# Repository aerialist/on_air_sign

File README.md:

# on_air_sign
An ON_AIR sign board with RGB LED matrix and a separate controller 

# make secret.py file
You would need to make secret.py file with following contents:

secrets = {
    'ssid' : 'yourssid', # home wifi access point ssid
    'password' : 'ssidpassword', # password for ssid
    'timezone' : "Asia/Tokyo", # http://worldtimeapi.org/timezones
    'aio_username': "aiouser", # Adafruit IO user name
    'aio_password': "aiokey", # Adafruit IO password
    'broker': "awsiotxxx.amazonaws.com", # AWS IoT Device data endpoint
    "client_id": "on_air_sign_featherm4", # AWS IoT Things name for testing
    "client_id_controller": "on_air_sign_controller", # AWS IoT Things name for controller
    "client_id_matrix": "on_air_sign_matrix", # AWS IoT Things name for matrix
}

# copy AWS IoT device certificates and private keys

Define AWS IoT Thing for controller and matrix. Download device certificates and private keys in aws folder.

aws/aws_cert_controller.pem.crt
aws/aws_cert_matrix.pem.crt
aws/private_controller.pem.key
aws/private_matrix.pem.key

# code to use Adafruit IO

code_controller.py
code_matrix.py

Copy them as code.py to controller and matrix.

# code to use AWS IoT

code_controller_aws.py
code_matrix_aws.py

Copy them as code.py to controller and matrix.

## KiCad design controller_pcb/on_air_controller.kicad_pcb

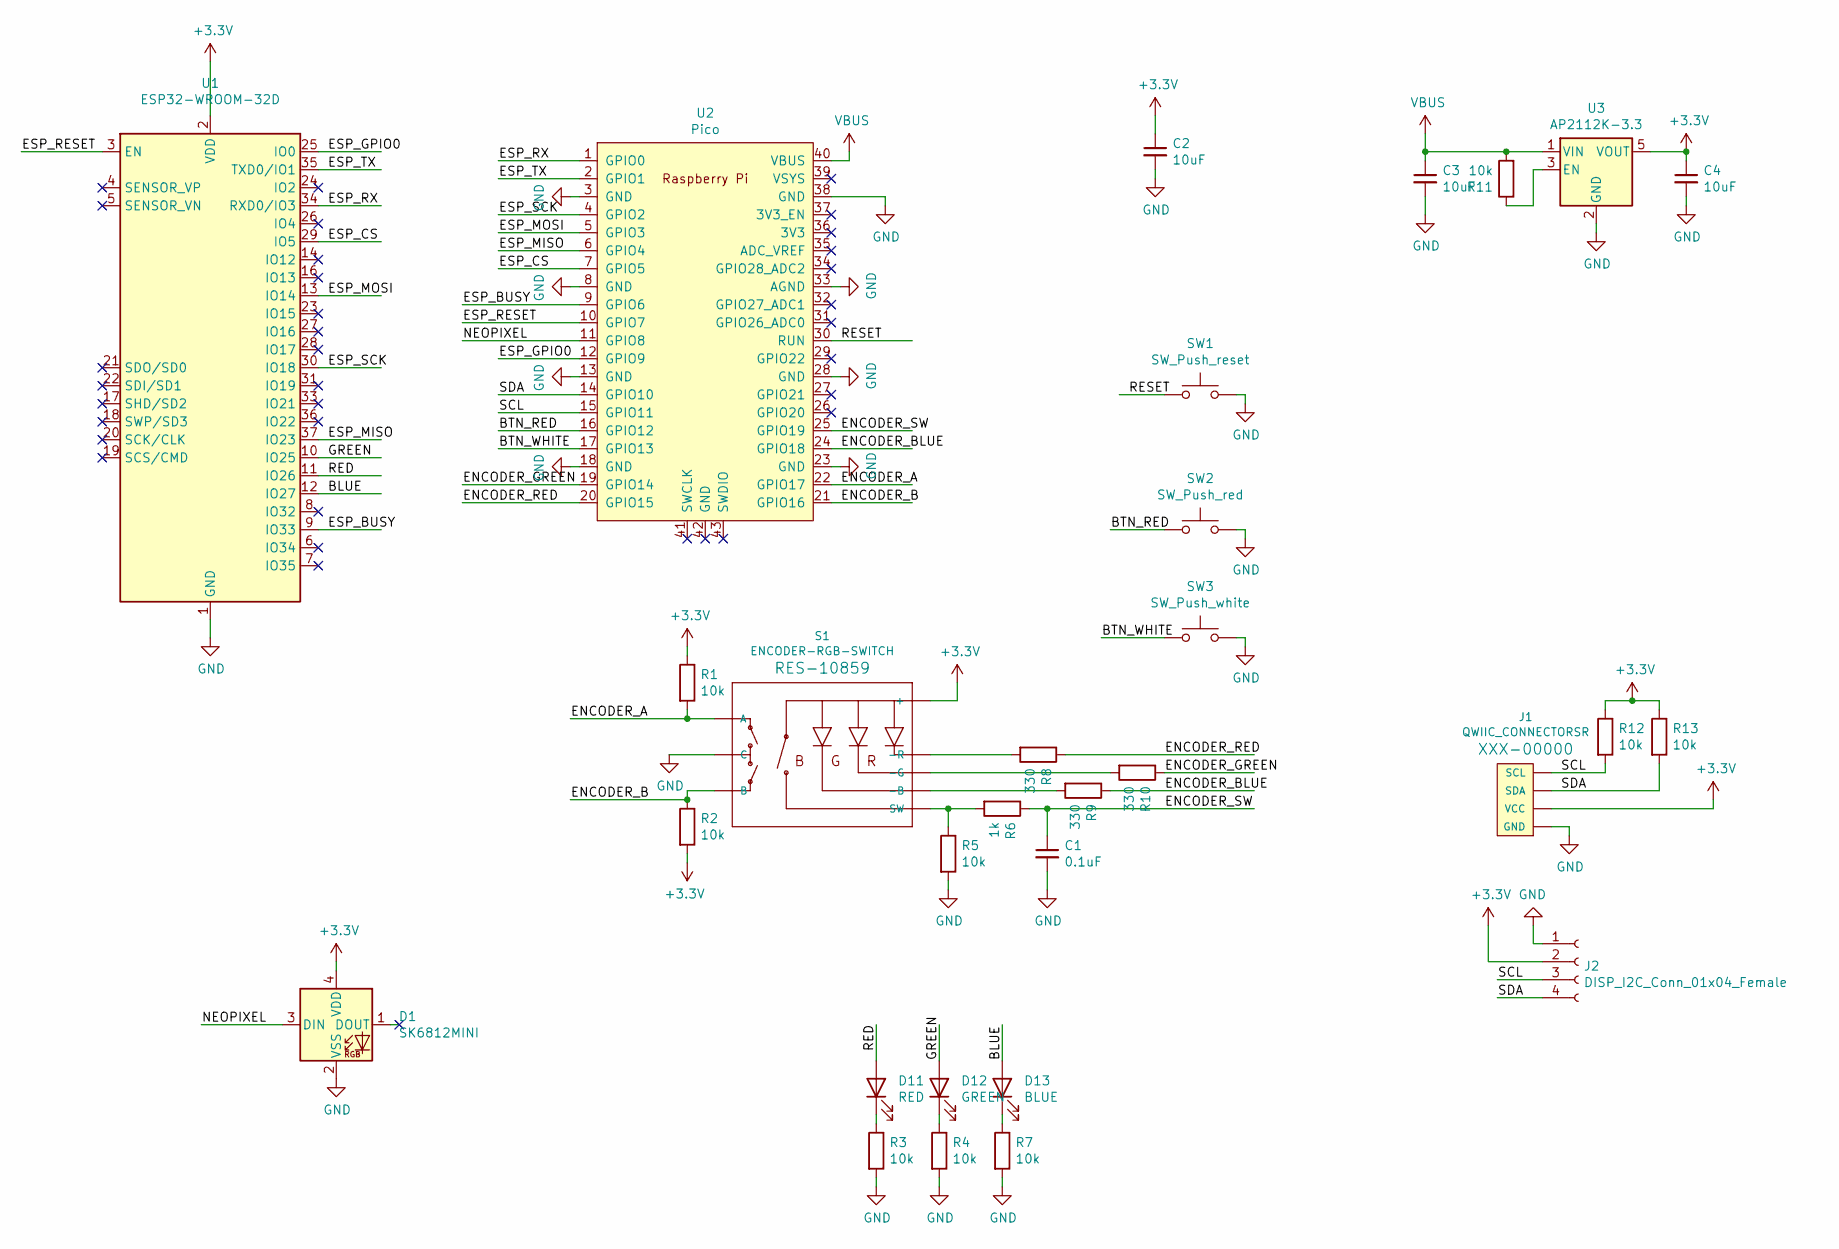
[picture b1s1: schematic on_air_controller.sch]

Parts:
C1: 0.1uF; C_0805_2012Metric_Pad1.18x1.45mm_HandSolder
C2, C3, C4: 10uF; C_0805_2012Metric_Pad1.18x1.45mm_HandSolder
D1: SK6812MINI; LED_SK6812MINI_PLCC4_3.5x3.5mm_P1.75mm
D11: RED; LED_1206_3216Metric_Pad1.42x1.75mm_HandSolder
D12: GREEN; LED_1206_3216Metric_Pad1.42x1.75mm_HandSolder
D13: BLUE; LED_1206_3216Metric_Pad1.42x1.75mm_HandSolder
J1: QWIIC_CONNECTORSR; 1X04_1MM_RA_STRESSRELIEF
J2: DISP_I2C_Conn_01x04_Female; OLED_0.96inch_PinHeader_1x04_P2.54mm_Vertical
R1, R2, R3, R4, R5, R7, R11, R12, R13: 10k; R_0805_2012Metric_Pad1.20x1.40mm_HandSolder
R6: 1k; R_0805_2012Metric_Pad1.20x1.40mm_HandSolder
R8, R9, R10: 330; R_0805_2012Metric_Pad1.20x1.40mm_HandSolder
S1: ENCODER-RGB-SWITCH; ENCODER_LED_3
SW1: SW_Push_reset; SW_Push_1P1T_NO_CK_KMR2
SW2: SW_Push_red; SW_Cherry_MX_1.00u_PCB
SW3: SW_Push_white; SW_Cherry_MX_1.00u_PCB
U1: ESP32-WROOM-32D; ESP32-WROOM-32
U2: Pico; RPi_Pico_SMD_TH
U3: AP2112K-3.3; SOT-23-5

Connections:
+3V3: C2.1, C4.1, D1.4 (VDD), J1.2 (VCC), J2.2, R1.1, R2.2, R12.1, R13.1, S1.5 (+), U1.2 (VDD), U3.5 (VOUT)
/BLUE: D13.2 (A), U1.12 (IO27)
/BTN_RED: SW2.1, U2.16 (GPIO12)
/BTN_WHITE: SW3.1, U2.17 (GPIO13)
/ENCODER_A: R1.2, S1.A, U2.22 (GPIO17)
/ENCODER_B: R2.1, S1.B, U2.21 (GPIO16)
/ENCODER_BLUE: R9.1, U2.24 (GPIO18)
/ENCODER_GREEN: R10.1, U2.19 (GPIO14)
/ENCODER_RED: R8.1, U2.20 (GPIO15)
/ENCODER_SW: C1.1, R6.1, U2.25 (GPIO19)
/ESP_BUSY: U1.9 (IO33), U2.9 (GPIO6)
/ESP_CS: U1.29 (IO5), U2.7 (GPIO5)
/ESP_GPIO0: U1.25 (IO0), U2.12 (GPIO9)
/ESP_MISO: U1.37 (IO23), U2.6 (GPIO4)
/ESP_MOSI: U1.13 (IO14), U2.5 (GPIO3)
/ESP_RESET: U1.3 (EN), U2.10 (GPIO7)
/ESP_RX: U1.34 (RXD0/IO3), U2.1 (GPIO0)
/ESP_SCK: U1.30 (IO18), U2.4 (GPIO2)
/ESP_TX: U1.35 (TXD0/IO1), U2.2 (GPIO1)
/GREEN: D12.2 (A), U1.10 (IO25)
/NEOPIXEL: D1.3 (DIN), U2.11 (GPIO8)
/RED: D11.2 (A), U1.11 (IO26)
/RESET: SW1.1, U2.30 (RUN)
/SCL: J1.4 (SCL), J2.3, R12.2, U2.15 (GPIO11)
/SDA: J1.3 (SDA), J2.4, R13.2, U2.14 (GPIO10)
GND: C1.2, C2.2, C3.2, C4.2, D1.2 (VSS), J1.1 (GND), J2.1, R3.2, R4.2, R5.2, R7.2, S1.C, SW1.2, SW2.2, SW3.2, U1.1 (GND), U1.15 (GND), U1.38 (GND), U1.39 (GND), U2.3 (GND), U2.8 (GND), U2.13 (GND), U2.18 (GND), U2.23 (GND), U2.28 (GND), U2.33 (AGND), U2.38 (GND), U3.2 (GND)
unnamed: D11.1 (K), R3.1
unnamed: D12.1 (K), R4.1
unnamed: D13.1 (K), R7.1
unnamed: R5.1, R6.2, S1.3 (SW)
unnamed: R8.2, S1.1 (-R)
unnamed: R9.2, S1.4 (-B)
unnamed: R10.2, S1.2 (-G)
unnamed: R11.1, U3.3 (EN)
VBUS: C3.1, R11.2, U2.40 (VBUS), U3.1 (VIN)

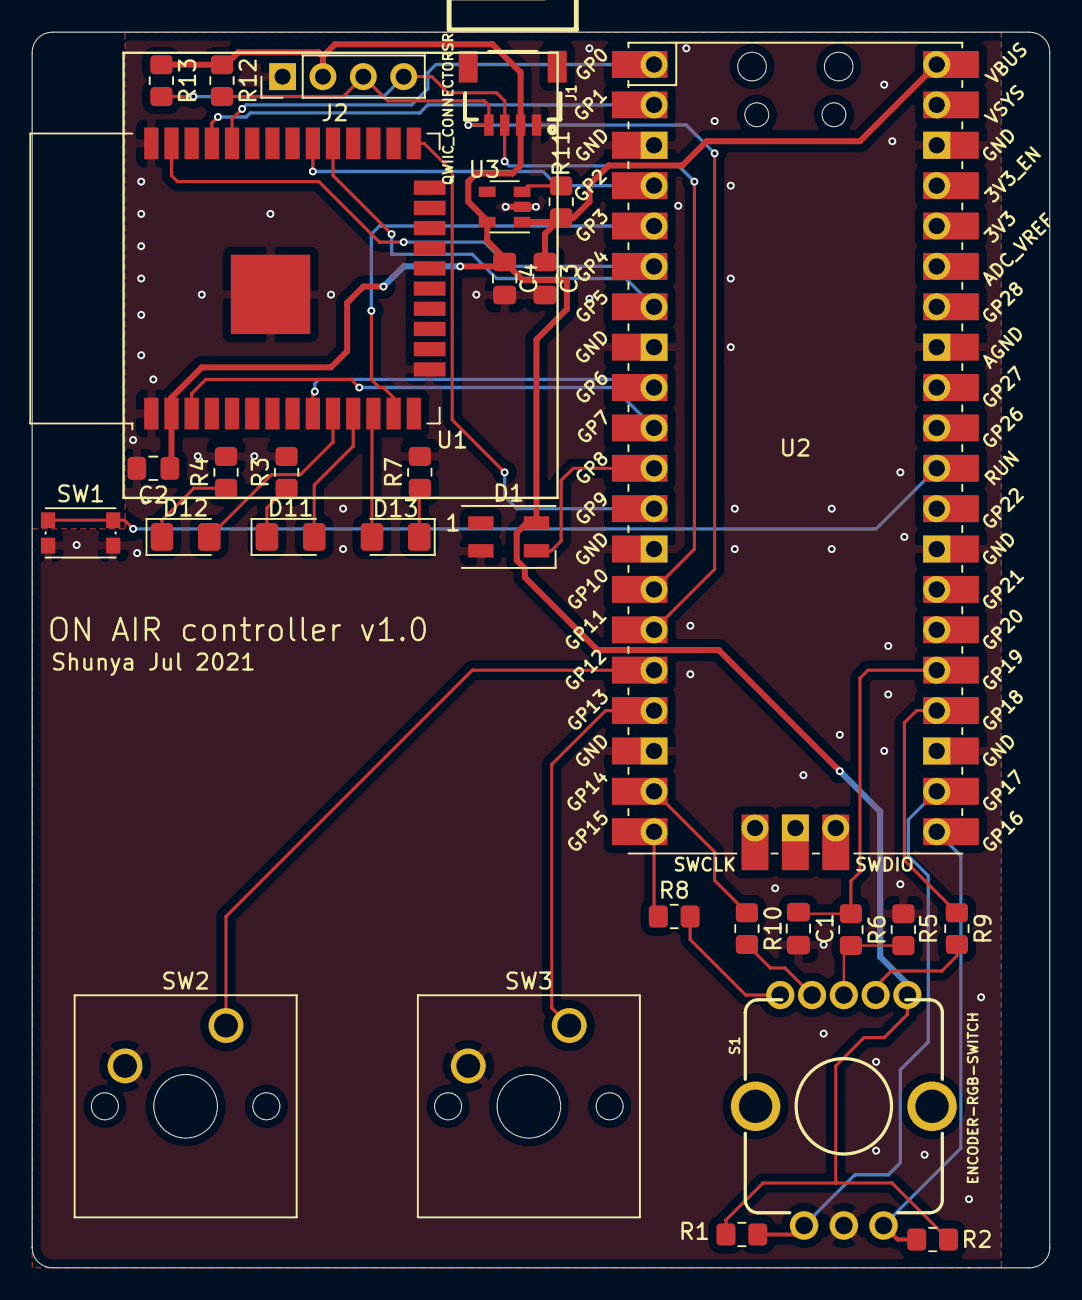
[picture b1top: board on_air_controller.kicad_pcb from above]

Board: 2 copper layers, 64.0 x 77.7 mm, 30 parts (0 on the bottom side), 35 nets.

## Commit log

2021-08-15 v1.0
2021-09-23 Add mech
